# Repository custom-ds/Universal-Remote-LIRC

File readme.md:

# Pi Remote

## Hardware
Display is based on the Raspberry Pi Touch Display 2, which is a 720x1280 pixels.

## Installing on a Pi
There is an installation script that handles most of the setup on the Raspberry Pi.

Use the Raspberry Pi Imager to install the base load of Raspberry Pi OS. This has been tested on a Pi 3 and Pi 4.

 - Install the 64 bit version of the operating system.
 - Set the time zone and keyboard layout as appropriate.
 - Set a hostname
 - Add a username, and set a password on it.
 - Configure the Wifi network.
 - Enable SSH access with password authentication.

Write out the image to the MicroSD card. Insert the card into the Raspberry Pi, then complete the assembly of the screen to the Pi. Attach the Pi daughter board to interface off to the 

Be sure to include the power cable as well as the ribbon cable. Attach the

Once assembly is completed, boot the Pi up

SSH into the new Pi computer using another PC. Update the core operating system before proceeding.

 - sudo apt update
 - sudo apt upgrade -y

RUN THE PACKAGE.PS1

COPY package.zip to the /home/{username}

```
unzip package.zip
chmod u+x install.sh
sudo .\install.sh
```

## Rasperry Pi Configuration
These are the manual steps required. If you use the `install.sh`, then these steps are generally taken care of for you, and you can skip this section. 

Install the required packages
```
sudo apt install xprintidle brightnessctl
sudo apt install python3-pillow
sudo apt install lirc
sudo apt install vim
```

Configure the Pi to use the GPIO port to send and receive IR signals

`sudo vi /boot/firmware/config.txt`

Add these two lines to the bottom of the config.txt file

```
dtoverlay=gpio-ir-tx,gpio_pin=17
dtoverlay=gpio-ir,gpio_pin=18
```

Save the file, then reboot the Raspberry Pi.

`sudo shutdown -r now`

You should be able to test the IR receiver. The basic form of that is to use the mode2 program to read in the gaps between the pulses and spaces.

`mode2 -d /dev/lirc0`

Note that it is possible that the devices have been created in other orders, and you may need to modify the device with something like `mode2 -d /dev/lirc1`. Check the /dev/ directory for possible options.

`ls /dev/lirc*`

### Screen Configuration
Resolution will automatically set, but the rotation angle needs to be corrected for the portrait mode.

Inside of the Raspbian GUI, go to Preferences -> Screen Configuration. Select DSI-1 from the screens list, and drill into Orientation and select Right.

Click the Apply button, and the confirm the change.

## LIRC Configurations

LIRC Remote repositories:
 - https://lirc-remotes.sourceforge.net/remotes-table.html

wget https://sourceforge.net/p/lirc-remotes/code/ci/master/tree/remotes/philips/TIVO34.lircd.conf?format=raw -Otivo34.lircd.conf

## Installing the Daemon
The GUI runs as a daemon that will automatically start when the Pi boots up. If the script crashes for any reason, the daemon will automatically restart itself.

Copy the remote.service file into /etc/systemd/system/ folder.

Configure the daemon to start on boot up.

```
sudo systemctl daemon-reload
sudo systemctl enable remote.service
```

You can start and stop the daemon by running:

```
systemctl start remote
systemctl stop remote
```

## Recording Unknown Remotes

Most of the mainstream remotes can be found in the LIRC repositories around the Internet, but certain less-known remotes either aren't there, or are hidden among random names of companies that might not even be around anymore.

To record, you'll use the Infrared Receiver, along with the irrecord program. irrecord will guide you through the process, which basically involves starting the recording, then pushing the buttons on the remote enough times that it generates templates of the various sequences.

Before you get started though, you should be aware of the standard naming convention for the key presses. It's possible to rename these outstand of the standards, but that requires an extra switch. To get the full list of possible buttons, type:

`irrecord --list-namespace`

To start recording, type `irrecord -d /dev/lirc0 myRemote.conf` and follow the prompts, where myRemote is a descriptive name of the specific remote or product that you are recording for.

Once it is finished recording, move the resulting .conf file into /etc/lirc/lircd.conf.d/, then restart the lirc services.

`systemctl restart lircd`

You should be able to see the new remote when you list the remotes.

`irsend LIST "" ""`

Then you can list the specific buttons available for the new remote, by listing that configuration.

`irsend LIST "myRemote" ""`

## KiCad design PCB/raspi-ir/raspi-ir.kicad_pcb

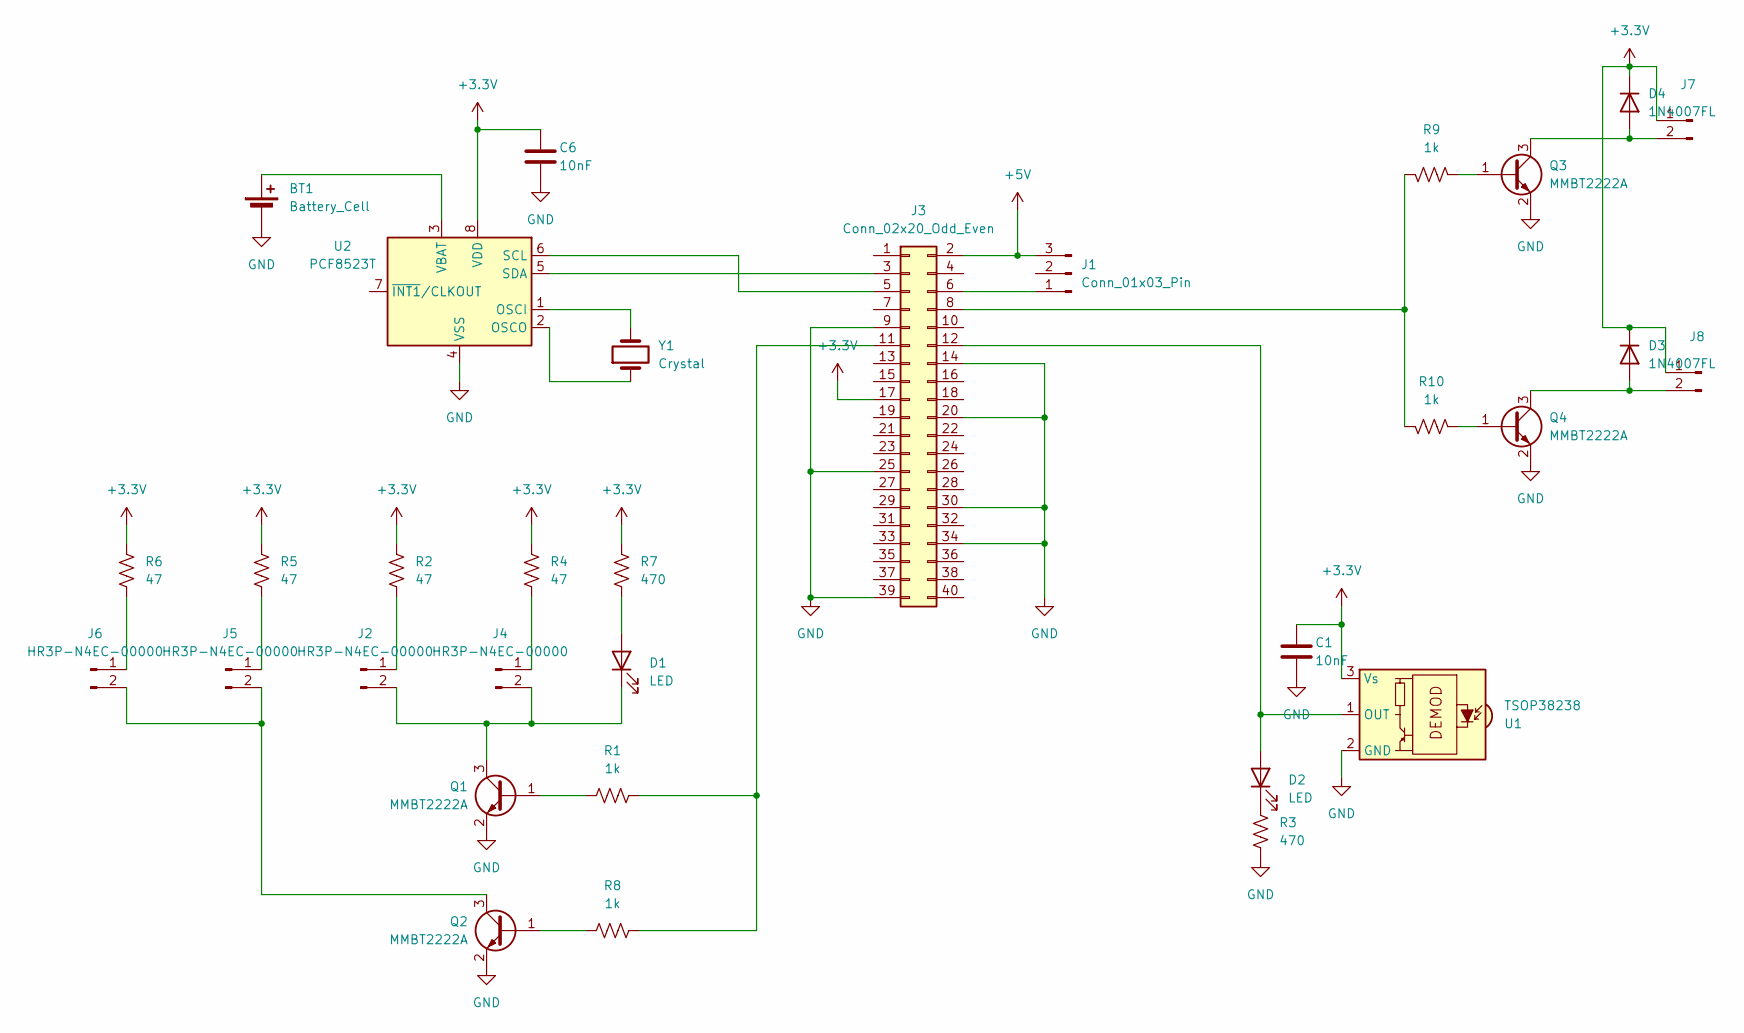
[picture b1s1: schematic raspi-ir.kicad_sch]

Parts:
BT1: Battery_Cell; BatteryHolder_Keystone_3000_1x12mm
C1, C6: 10nF; C_0805_2012Metric; Digikey 399-1158-1-ND
D1, D2: LED; D_0805_2012Metric
D3, D4: 1N4007FL; D_SOD-123; Digikey 1655-1N4007FLCT-ND
J1: Conn_01x03_Pin; PinSocket_1x03_P2.54mm_Horizontal
J2, J4, J5, J6: HR3P-N4EC-00000; PinHeader_1x02_P2.54mm_Horizontal; Digikey 516-HR3P-N4EC-00000-ND
J3: Conn_02x20_Odd_Even; PinHeader_2x20_P2.54mm_Vertical
J7, J8: PinHeader_1x02_P2.54mm_Horizontal; Digikey 516-HR3P-N4EC-00000-ND
Q1, Q2, Q3, Q4: MMBT2222A; SOT-23; Digikey 4878-MMBT2222ATR-ND
R1, R8, R9, R10: 1k; R_0805_2012Metric
R2, R4, R5, R6: 47; R_0805_2012Metric; Digikey RHM47BTR-ND
R3, R7: 470; R_0805_2012Metric
U1: TSOP38238; Vishay_MINICAST-3Pin; Digikey 751-1227-ND
U2: PCF8523T; SOIC-8_3.9x4.9mm_P1.27mm; Digikey 568-5306-2-ND
Y1: Crystal; Crystal_SMD_3215-2Pin_3.2x1.5mm; Digikey 535-9543-2-ND

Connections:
+3.3V: C1.1, C6.1, D3.1 (K), D4.1 (K), J3.17, J7.1, J8.1, R2.1, R4.1, R5.1, R6.1, R7.1, U1.3 (Vs), U2.8 (VDD)
+5V: J1.3, J3.2
GND: BT1.2 (-), C1.2, C6.2, J3.9, J3.14, J3.20, J3.25, J3.30, J3.34, J3.39, Q1.2 (E), Q2.2 (E), Q3.2 (E), Q4.2 (E), R3.1, U1.2 (GND), U2.4 (VSS)
unnamed: BT1.1 (+), U2.3 (VBAT)
unnamed: D1.2 (A), R7.2
unnamed: D1.1 (K), J2.2, J4.2, Q1.3 (C)
unnamed: D2.2 (A), J3.12, U1.1 (OUT)
unnamed: D2.1 (K), R3.2
unnamed: D3.2 (A), J8.2, Q4.3 (C)
unnamed: D4.2 (A), J7.2, Q3.3 (C)
unnamed: J1.1, J3.6
unnamed: J2.1, R2.2
unnamed: J3.3, U2.5 (SDA)
unnamed: J3.5, U2.6 (SCL)
unnamed: J3.8, R9.2, R10.2
unnamed: J3.11, R1.2, R8.2
unnamed: J4.1, R4.2
unnamed: J5.1, R5.2
unnamed: J5.2, J6.2, Q2.3 (C)
unnamed: J6.1, R6.2
unnamed: Q1.1 (B), R1.1
unnamed: Q2.1 (B), R8.1
unnamed: Q3.1 (B), R9.1
unnamed: Q4.1 (B), R10.1
unnamed: U2.1 (OSCI), Y1.2
unnamed: U2.2 (OSCO), Y1.1

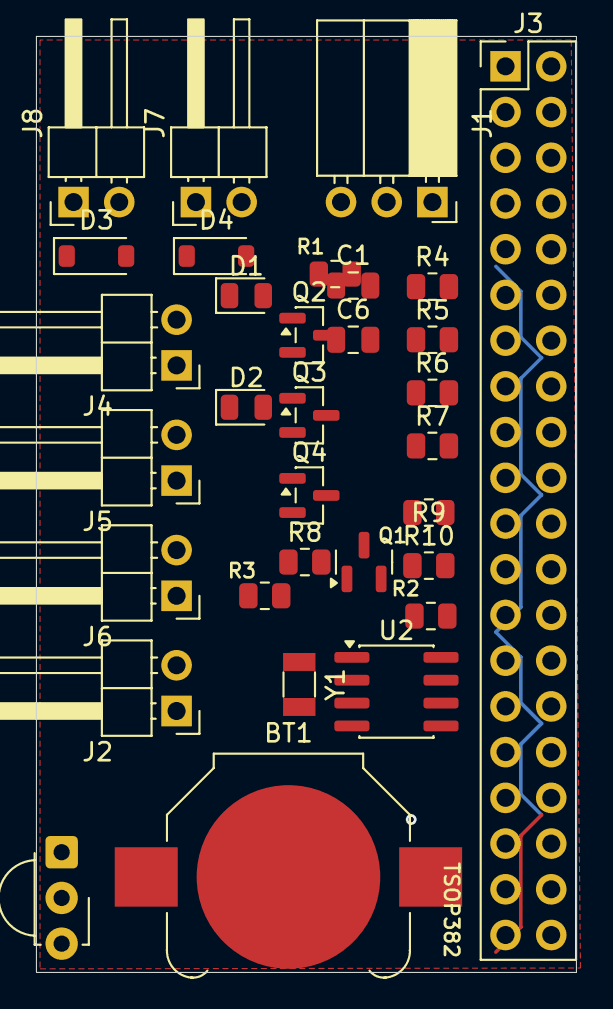
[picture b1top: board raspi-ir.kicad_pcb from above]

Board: 2 copper layers, 30.0 x 52.0 mm, 32 parts (0 on the bottom side), 26 nets.

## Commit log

2025-11-07 Reworked icons to be smaller and clearer. Added support for transparent .png buttons.
2025-11-07 Added 3d models for case
2025-11-09 New button renderings. Added lirc remotes.
2025-11-24 Added logical groupings
2025-11-25 Fixes and traps for quick repeating of buttons.
2025-11-30 Restructured icon files. Updating PCB with more features. Created conference room layout.
2025-12-02 Fix for fan position on case
2025-12-02 Updates to install scripts
2025-12-05 Updated conference-room template, created install scripts, finished STL files.
2025-12-08 PCB redesigned to version 2
2025-12-10 Updates to the conference screen, and fixes for the package and installer script.
2025-12-10 Additional round icons.
2025-12-14 New lid design with emiters in it.
2025-12-21 Fixes to home-theater
